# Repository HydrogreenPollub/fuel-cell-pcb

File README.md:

## Fuel cell control unit PCB

CADLAB preview: [link](https://cadlab.io/project/27518)

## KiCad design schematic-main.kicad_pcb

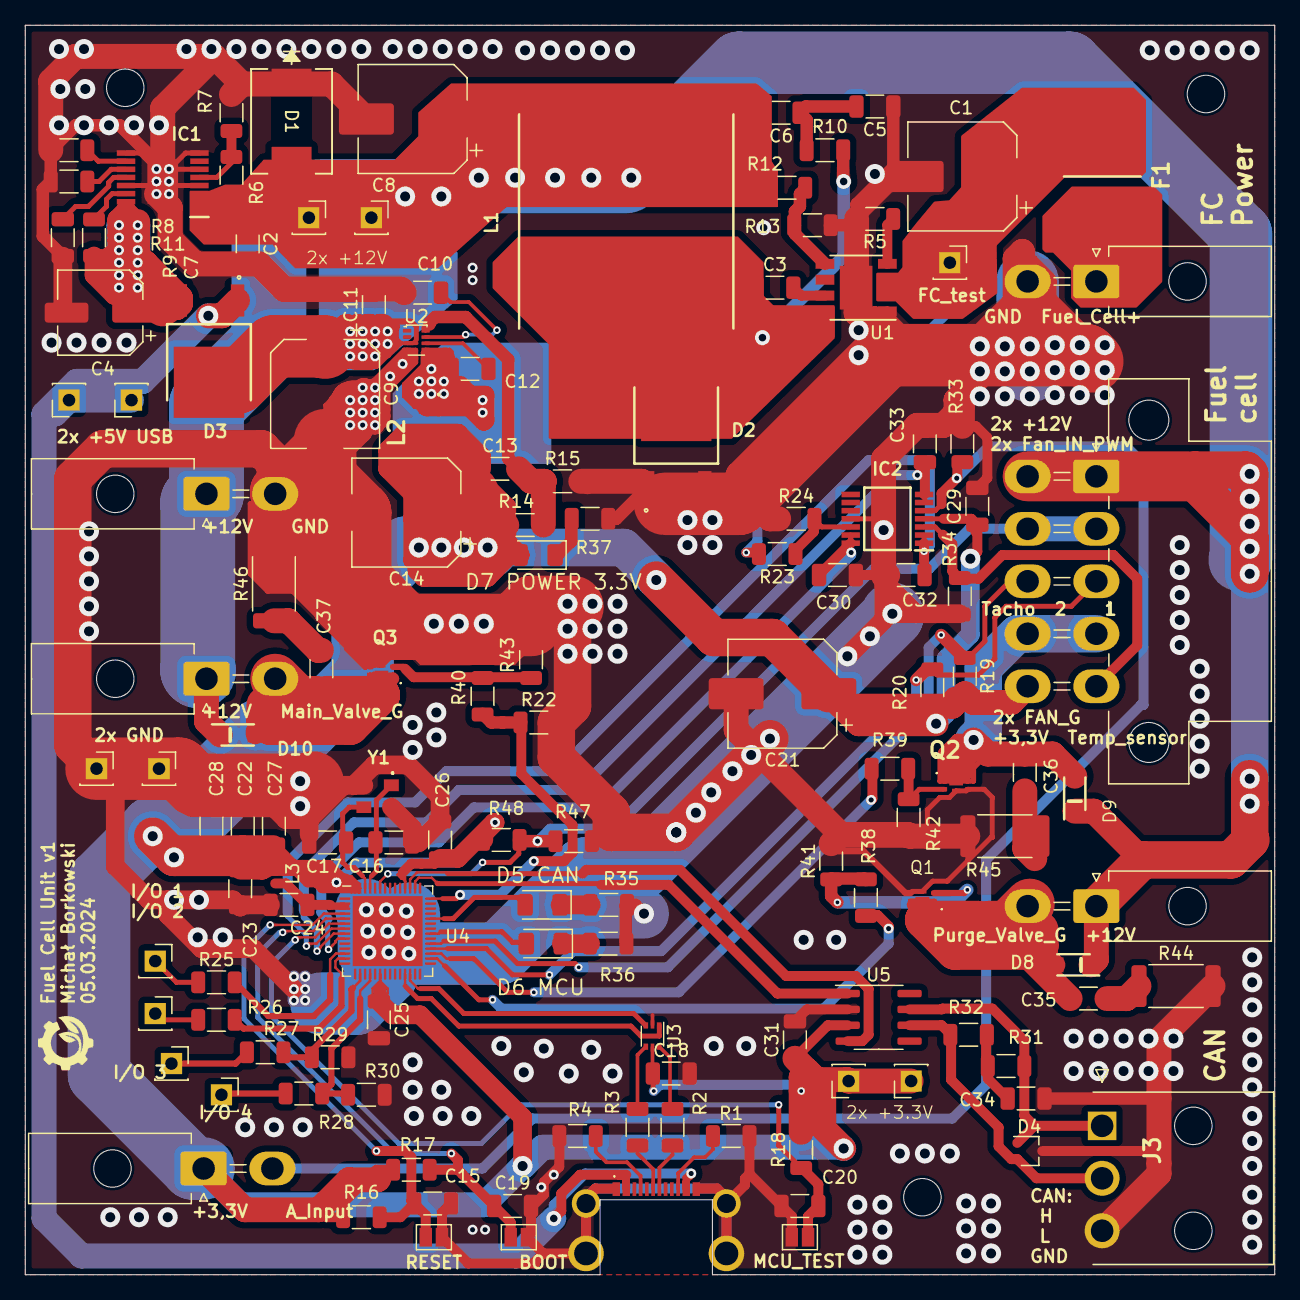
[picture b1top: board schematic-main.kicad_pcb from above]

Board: 2 copper layers, 100.0 x 100.0 mm, 133 parts (0 on the bottom side), 73 nets.

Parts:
C1, C9, C21: 10u; CP_Elec_8x10.5
C2, C15, C19, C20, C22, C27: 1u; C_1206_3216Metric
C3: 2n2; C_1206_3216Metric
C4: 47u; CP_Elec_6.3x7.7
C5, C13: 47p; C_1206_3216Metric
C6: 3n3; C_1206_3216Metric
C7: 2n7; C_1206_3216Metric
C8: 22u; CP_Elec_8x10.5
C10: 33n; C_1206_3216Metric
C11, C12, C18, C23, C24, C25, C26, C29, C31: 100n; C_1206_3216Metric
C14: 100u; CP_Elec_8x10.5
C16, C17: 12p; C_1206_3216Metric
C28: 10n; C_1206_3216Metric
C30, C32, C33, C34: 4n7; C_1206_3216Metric
C35, C36, C37: 20n; C_1206_3216Metric
D1: TPSMC30CA; TPSMCSeries_LTF
D2, D3: MBRD20100CT-13; TO252_(DPAK)_1
D4: SP0502BAJT; SOT-323_SC-70
D5 CAN, D6 MCU, D7 POWER 3.3V: LED; LED_1206_3216Metric
D8, D9, D10: PMEG10020; PMEG10020ELR
F1: 3A; FUSC8664X180N
IC1: LM76202QPWPRQ1; SOP65P640X120-17N
IC2: AD8544ARUZ-REEL; SOP65P640X120-14N
J1: Fell_Cell_IN; Molex_Mini-Fit_Jr_5569-02A2_2x01_P4.20mm_Horizontal
J2: Analog_In; Molex_Mini-Fit_Jr_5569-02A2_2x01_P4.20mm_Horizontal
J3: CAN; 39303035
J4: Axilary_Out; Molex_Mini-Fit_Jr_5569-02A2_2x01_P4.20mm_Horizontal
J5: P_Valve; Molex_Mini-Fit_Jr_5569-02A2_2x01_P4.20mm_Horizontal
J6: Valve; Molex_Mini-Fit_Jr_5569-02A2_2x01_P4.20mm_Horizontal
J7: FC Cooling; Molex_Mini-Fit_Jr_5569-10A1_2x05_P4.20mm_Horizontal
JP1, JP2, JP3: SolderJumper_2_Open; SolderJumper-2_P1.3mm_Open_Pad1.0x1.5mm
L1: IHLP6767DZER470M11
L2: 4u7; SRN3015TA4R7M
L3: 2n; L_0402_1005Metric
P1: USB_C_Plug_USB2.0; 2169900002
Q1, Q2, Q3: PMPB10XNX; PMPB15XPAX
R1, R4: 5k1; R_1206_3216Metric
R2, R3: 0; R_1206_3216Metric
R5, R8, R9: 100k; R_1206_3216Metric
R6: 180k; R_1206_3216Metric
R7: 12k; R_1206_3216Metric
R10: 143k; R_1206_3216Metric
R11: 56k; R_1206_3216Metric
R12: 453k; R_1206_3216Metric
R13: 49k9; R_1206_3216Metric
R14: 32k; R_1206_3216Metric
R15, R16, R17, R18, R19, R20, R22, R23, R29, R30, R33, R41, R42, R43, R47, R48: 10k; R_1206_3216Metric
R24: 150k; R_1206_3216Metric
R25, R26, R35, R36, R37: 1k; R_1206_3216Metric
R27, R28: 100R; R_1206_3216Metric
R31, R32: 60; R_1206_3216Metric
R34: 560k; R_1206_3216Metric
R38, R39, R40: 180R; R_1206_3216Metric
R44, R45, R46: 100R 0,5W; R_2512_6332Metric
TP1: I/O 1; PinSocket_1x01_P2.54mm_Vertical
TP1#2: FC test; PinSocket_1x01_P2.54mm_Vertical
TP2: I/O 2; PinSocket_1x01_P2.54mm_Vertical
TP2#2, TP3: GND; PinSocket_1x01_P2.54mm_Vertical
TP4, TP5: +12V; PinSocket_1x01_P2.54mm_Vertical
TP6, TP7: +5V; PinSocket_1x01_P2.54mm_Vertical
TP8, TP9: +3.3V; PinSocket_1x01_P2.54mm_Vertical
TP12: I/O 3; PinSocket_1x01_P2.54mm_Vertical
TP13: I/O 4; PinSocket_1x01_P2.54mm_Vertical
U1: LM5013DDAR; Diodes_SO-8EP
U2: TPS62933; SOT-583-8
U3: USBLC6-2P6; SOT-666
U4: ESP32-S3FN8; QFN-56-1EP_7x7mm_P0.4mm_EP5.6x5.6mm
U5: SN65HVD232; SOIC-8_3.9x4.9mm_P1.27mm
Y1: Crystal_GND24; KC3225K400000C1GE00

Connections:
+3.3V: C13.1, C14.1, C18.1, C21.1, C22.1, C23.1, C25.1, C26.1, C27.1, C28.1, C29.1, C31.1, D7 POWER 3.3V.2 (A), IC2.4 (V+), J2.1, J7.10, L2.2, L3.1, R14.1, R16.2, R17.2, R18.2, R19.2, R20.2, R48.2, TP8.1, TP9.1, U3.5 (VBUS), U4.20 (VDD3P3_RTC), U4.46 (VDD3P3_CPU), U4.55 (VDDA), U4.56 (VDDA), U5.3 (VCC)
+5V: D3.1, P1.A4 (VBUS), P1.A9 (VBUS), P1.B4 (VBUS), P1.B9 (VBUS), TP6.1, TP7.1
+12V: C2.1, C6.2, C8.1, D1.2 (A), D8.1 (K), D9.1 (K), D10.1 (K), IC1.1 (IN_1), IC1.2 (IN_2), IC1.3 (UVLO), J4.1, J5.1, J6.1, J7.1, J7.6, L1.2, R6.1, R12.2, TP4.1, TP5.1
/IO/A_Input: IC2.5 (+IN_B), J2.2, R33.1
/IO/Analog_MCU: C33.1, IC2.6 (-IN_B), IC2.7 (OUT_B), U4.8 (GPIO3/ADC1_CH2)
/IO/CANH: D4.1 (K), J3.1, R31.2, U5.7 (CANH)
/IO/CANL: D4.2 (K), J3.2, R32.2, U5.6 (CANL)
/IO/CAN_RX: U4.44 (MTCK/JTAG/GPIO39), U5.1 (D)
/IO/CAN_TX: U4.45 (MTDO/JTAG/GPIO40), U5.4 (R)
/IO/FAN_1_TACHO: J7.3, R20.1, U4.32 (SPICS0/GPIO29)
/IO/FAN_2_TACHO: J7.8, R19.1, U4.33 (SPICLK/GPIO30)
/IO/FAN_GND: C36.1, D9.2 (A), J7.4, J7.9, Q2.1 (D)
/IO/FAN_IN_PWM: J7.2, J7.7, R47.1, R48.1, U4.51 (GPIO45)
/IO/FAN_ON_MCU: R39.2, U4.31 (SPIWP/GPIO28)
/IO/FC_V: C1.1, F1.2, R23.2, TP1#2.1, U1.2 (VIN), U1.3 (EN_UVLO)
/IO/FC_Voltage_MCU: C30.2, IC2.13 (-IN_D), IC2.14 (OUT_D), U4.9 (GPIO4/ADC1_CH3)
/IO/I/O_1_MCU: R25.2, U4.12 (GPIO7/ADC1_CH6)
/IO/I/O_2_MCU: R26.2, U4.13 (GPIO8/ADC1_CH7)
/IO/I/O_3_MCU: R27.2, R29.1, U4.16 (GPIO11/ADC2_CH0)
/IO/I/O_4_MCU: R28.2, R30.1, U4.18 (GPIO13/ADC2_CH2)
/IO/LED_CAN_STATUS: D5 CAN.2 (A), U4.38 (GPIO33)
/IO/LED_MCU_STATUS: D6 MCU.2 (A), U4.35 (SPID/GPIO32)
/IO/Main_Valve: C37.1, D10.2 (A), J6.2, Q3.1 (D)
/IO/Main_Valve_MCU: R22.1, R40.2, U4.42 (GPIO37)
/IO/PURGE_VALVE: C35.1, D8.2 (A), J5.2, Q1.1 (D)
/IO/PURGE_VALVE_MCU: R38.2, U4.30 (SPIHD/GPIO27)
/IO/Temp_MCU: C32.2, IC2.1 (OUT_A), IC2.2 (-IN_A), U4.7 (GPIO2/ADC1_CH1)
/IO/Temp_sensor: IC2.3 (+IN_A), J7.5, R34.1
/MCU/BOOT: C19.1, JP2.1 (A), R17.1, U4.5 (GPIO0/BOOT)
/MCU/MCU_TEST: C20.1, JP3.1 (A), R18.1, U4.6 (GPIO1/ADC1_CH0)
/MCU/RESET: C15.1, JP1.1 (A), R16.1, U4.4 (CHIP_PU/RESET)
/MCU/USB_D+: R3.2, U3.3 (I/O2), U3.4 (I/O2), U4.26 (GPIO20/USB_D+/ADC2_CH9)
/MCU/USB_D-: R2.2, U3.1 (I/O1), U3.6 (I/O1), U4.25 (GPIO19/USB_D-/ADC2_CH8)
/MCU/XTAL_N: C16.1, U4.53 (XTAL_N), Y1.1
/MCU/XTAL_P: C17.1, U4.54 (XTAL_P), Y1.3
/Power /FB_12: R12.1, R13.2, U1.5 (FB)
/Power /Vin: F1.1, J1.1
/Power /Vreg: C4.1, D3.2, IC1.15 (OUT_1), IC1.16 (OUT_2), R9.1
GND: C1.2, C2.2, C4.2, C5.1, C7.2, C8.2, C9.2, C10.2, C11.2, C14.2, C15.2, C16.2, C17.2, C18.2, C19.2, C20.2, C21.2, C22.2, C23.2, C24.2, C25.2, C26.2, C27.2, C28.2, C29.2, C30.1, C31.2, C32.1, C33.2, C34.2, D1.1 (K), D2.1 (A_1), D2.2 (A_2), D4.3 (A), IC1.4 (NC_1), IC1.6 (MODE), IC1.8 (RTN), IC1.9 (GND), IC1.13 (NC_2), IC1.17 (EP), IC2.11 (GND), J1.2, J3.3, J4.2, JP1.2 (B), JP2.2 (B), JP3.2 (B), P1.A1 (GND), P1.A12 (GND), P1.B1 (GND), P1.B12 (GND), Q1.3 (S), Q2.3 (S), Q3.3 (S), R1.2, R4.2, R5.2, R7.2, R8.2, R11.2, R13.1, R15.2, R22.2, R24.1, R29.2, R30.2, R33.2, R34.2, R35.2, R36.2, R37.2, R41.2, R42.2, R43.2, R44.2, R45.2, R46.2, R47.2, TP2#2.1, TP3.1, U1.1 (GND), U1.9 (EP), U2.4 (GND), U3.2 (GND), U4.57 (GND), U5.2 (GND), Y1.2, Y1.4
unnamed: C5.2, C6.1, R10.2
unnamed: C34.1, R31.1, R32.1
unnamed: C35.2, R44.1
unnamed: C36.2, R45.1
unnamed: C37.2, R46.1
unnamed: C3.1, D2.3 (K), L1.1, R10.1, U1.8 (SW)
unnamed: D5 CAN.1 (K), R35.1
unnamed: D6 MCU.1 (K), R36.1
unnamed: D7 POWER 3.3V.1 (K), R37.1
unnamed: C7.1, IC1.12 (DVDT)
unnamed: IC1.11 (ILIM), R11.1
unnamed: IC1.10 (IMON), R8.1
unnamed: IC1.5 (OVP), R6.2, R7.1
unnamed: IC1.14 (~FLT), R9.2
unnamed: IC2.12 (+IN_D), R23.1, R24.2
unnamed: P1.A5 (CC), R4.1
unnamed: P1.A6 (D+), R3.1
unnamed: P1.A7 (D-), R2.1
unnamed: P1.B5 (VCONN), R1.1
unnamed: Q1.2 (G), R38.1, R41.1
unnamed: Q2.2 (G), R39.1, R42.1
unnamed: Q3.2 (G), R40.1, R43.1
unnamed: R25.1, TP1.1
unnamed: R26.1, TP2.1
unnamed: R27.1, TP12.1
unnamed: R28.1, TP13.1
unnamed: C3.2, U1.7 (BST)
unnamed: R5.1, U1.4 (RON)
unnamed: C12.1, U2.6 (BST)
unnamed: C13.2, R14.2, R15.1, U2.8 (FB)
unnamed: C10.1, U2.7 (SS)
unnamed: C12.2, L2.1, U2.5 (SW)
unnamed: C9.1, C11.1, D3.3, U2.3 (VIN)
VDD3P3: C24.1, L3.2, U4.2 (VDD3P3), U4.3 (VDD3P3)

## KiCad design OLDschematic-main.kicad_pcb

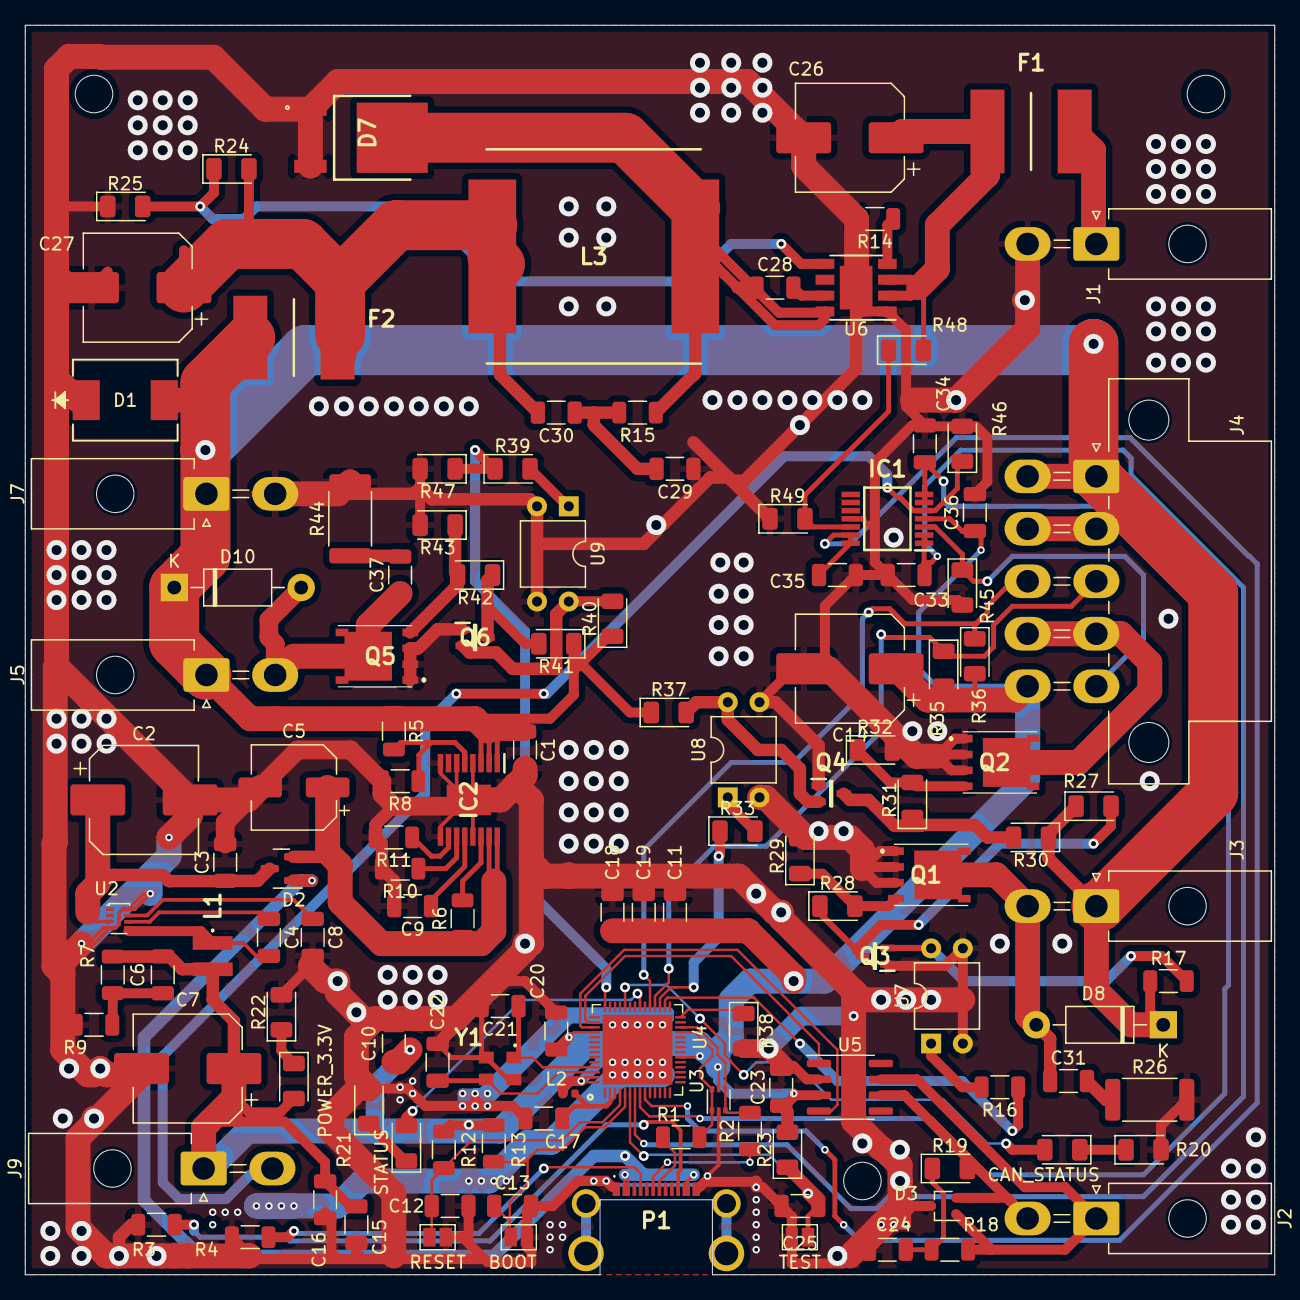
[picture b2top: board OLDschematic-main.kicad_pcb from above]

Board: 2 copper layers, 100.0 x 100.0 mm, 126 parts (0 on the bottom side), 75 nets.

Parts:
BOOT: SolderJumper_2_Open; SolderJumper-2_P1.3mm_Open_Pad1.0x1.5mm
C1, C12, C13, C15, C18, C25: 1u; C_1206_3216Metric
C2, C14, C26: 10u; CP_Elec_8x10.5
C3, C4, C10, C11, C16, C17, C20, C23, C36: 100n; C_1206_3216Metric
C5: 47u; CP_Elec_6.3x7.7
C6, C29: 47p; C_1206_3216Metric
C7: 100u; CP_Elec_8x10.5
C8: 33n; C_1206_3216Metric
C9: 2n7; C_1206_3216Metric
C19: 10n; C_1206_3216Metric
C21, C22: 12p; C_1206_3216Metric
C24, C33, C34, C35: 4n7; C_1206_3216Metric
C27: 22u; CP_Elec_8x10.5
C28: 2n2; C_1206_3216Metric
C30: 3n3; C_1206_3216Metric
C31, C37: 20n; C_1206_3216Metric
CAN_STATUS: LED; D_1206_3216Metric
D1: TPSMC30CA; TPSMCSeries_LTF
D2: BAS40-05; SOT-23
D3: SP0502BAJT; SOT-323_SC-70
D7: MBRD20100CT-13; TO252_(DPAK)_1
D8, D10: 1N5819; D_DO-41_SOD81_P10.16mm_Horizontal
F1, F2: 3A; FUSC8664X180N
IC1: AD8544ARUZ-REEL; SOP65P640X120-14N
IC2: LM76202QPWPRQ1; SOP65P640X120-17N
J1: Fell_Cell_IN; Molex_Mini-Fit_Jr_5569-02A2_2x01_P4.20mm_Horizontal
J2: CAN; Molex_Mini-Fit_Jr_5569-02A2_2x01_P4.20mm_Horizontal
J3: P_Valve; Molex_Mini-Fit_Jr_5569-02A2_2x01_P4.20mm_Horizontal
J4: FC Cooling; Molex_Mini-Fit_Jr_5569-10A1_2x05_P4.20mm_Horizontal
J5: Valve; Molex_Mini-Fit_Jr_5569-02A2_2x01_P4.20mm_Horizontal
J7: Axilary_Out; Molex_Mini-Fit_Jr_5569-02A2_2x01_P4.20mm_Horizontal
J9: Analog_In; Molex_Mini-Fit_Jr_5569-02A2_2x01_P4.20mm_Horizontal
L1: 4u7; SRN3015TA4R7M
L2: 2n; L_0402_1005Metric
L3: IHLP6767DZER470M11
P1: USB_C_Plug_USB2.0; 2169900002
POWER_3.3V: LED; D_1206_3216Metric
Q1, Q2, Q5: SIR186LDP-T1-RE3; SI7141DPT1GE3
Q3, Q4, Q6: 2N3904; SOT65P220X100-3N
R1, R2: 0; R_1206_3216Metric
R3, R4: 5k1; R_1206_3216Metric
R5: 180k; R_1206_3216Metric
R6, R11, R14: 100k; R_1206_3216Metric
R7: 32k; R_1206_3216Metric
R8: 12k; R_1206_3216Metric
R9, R12, R13: 10k; R_1206_3216Metric
R10: 56k; R_1206_3216Metric
R15: 143k; R_1206_3216Metric
R16: 100; R_1206_3216Metric
R17: 1k; R_1206_3216Metric
R18: 60; R_1206_3216Metric
R19: 60; LED_1206_3216Metric
R20, R21, R22, R27, R30, R37, R40, R41: 1k; LED_1206_3216Metric
R23, R29, R32, R35, R36, R38, R43, R46, R47, R48: 10k; LED_1206_3216Metric
R24: 453k; LED_1206_3216Metric
R25: 49k9; LED_1206_3216Metric
R26, R44: 100R 0,5W; R_2512_6332Metric
R28, R31, R33, R39, R42: 100; LED_1206_3216Metric
R45: 560k; LED_1206_3216Metric
R49: 150k; LED_1206_3216Metric
RESET: SolderJumper_2_Open; SolderJumper-2_P1.3mm_Open_Pad1.0x1.5mm
STATUS: LED; D_1206_3216Metric
TEST: SolderJumper_2_Open; SolderJumper-2_P1.3mm_Open_Pad1.0x1.5mm
U2: TPS62933; SOT-583-8
U3: USBLC6-2P6; SOT-666
U4: ESP32-S3FN8; QFN-56-1EP_7x7mm_P0.4mm_EP5.6x5.6mm
U5: SN65HVD232; SOIC-8_3.9x4.9mm_P1.27mm
U6: LM5013DDAR; Diodes_SO-8EP
U7, U8, U9: PC817; DIP-4_W7.62mm
Y1: Crystal_GND24; KC3225K400000C1GE00

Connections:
+3.3V: C6.1, C7.1, C10.1, C11.1, C14.1, C15.1, C16.1, C18.1, C19.1, C20.1, C23.1, C36.1, IC1.4 (V+), J4.10, J9.1, L1.2, L2.1, POWER_3.3V.2 (A), R7.1, R12.2, R13.2, R23.2, R35.2, R36.2, U3.5 (VBUS), U4.20 (VDD3P3_RTC), U4.46 (VDD3P3_CPU), U4.55 (VDDA), U4.56 (VDDA), U5.3 (VCC)
+12V: C1.1, D1.2 (A), D8.1 (K), D10.1 (K), F2.2, IC2.1 (IN_1), IC2.2 (IN_2), IC2.3 (UVLO), J3.1, J4.1, J4.6, J5.1, J7.1, R5.1, R17.1, R27.1, R30.1, R37.1, R40.1, R41.1
/FAN_PWM: J4.2, J4.7
/IO/A_Input: IC1.5 (+IN_B), J9.2, R46.1
/IO/Analog_MCU: C34.1, IC1.6 (-IN_B), IC1.7 (OUT_B), U4.8 (GPIO3/ADC1_CH2)
/IO/CANH: D3.1 (K), J2.1, R18.2, U5.7 (CANH)
/IO/CANL: D3.2 (K), J2.2, R19.2, U5.6 (CANL)
/IO/CAN_RX: U4.44 (MTCK/JTAG/GPIO39), U5.1 (D)
/IO/CAN_TX: U4.45 (MTDO/JTAG/GPIO40), U5.4 (R)
/IO/FAN_1_TACHO: J4.3, R35.1, U4.32 (SPICS0/GPIO29)
/IO/FAN_2_TACHO: J4.8, R36.1, U4.33 (SPICLK/GPIO30)
/IO/FAN_GND: J4.4, J4.9, Q2.5 (D_1), Q2.6 (D_2), Q2.7 (D_3), Q2.8 (D_4), Q2.9 (D_5), Q2.10 (D_6), Q2.11 (D_7)
/IO/FAN_ON_MCU: R33.1, U4.31 (SPIWP/GPIO28)
/IO/FC_Voltage_MCU: C35.2, IC1.13 (-IN_D), IC1.14 (OUT_D), U4.9 (GPIO4/ADC1_CH3)
/IO/LED_CAN_STATUS: CAN_STATUS.2 (A), U4.38 (GPIO33)
/IO/LED_MCU_STATUS: STATUS.2 (A), U4.35 (SPID/GPIO32)
/IO/Main_Valve: C37.1, D10.2 (A), J5.2, Q5.5 (D_1), Q5.6 (D_2), Q5.7 (D_3), Q5.8 (D_4), Q5.9 (D_5), Q5.10 (D_6), Q5.11 (D_7)
/IO/Main_Valve_MCU: R39.1, R47.1, U4.42 (GPIO37)
/IO/PURGE_VALVE: C31.1, D8.2 (A), J3.2, Q1.5 (D_1), Q1.6 (D_2), Q1.7 (D_3), Q1.8 (D_4), Q1.9 (D_5), Q1.10 (D_6), Q1.11 (D_7)
/IO/PURGE_VALVE_MCU: R16.1, U4.30 (SPIHD/GPIO27)
/IO/SC_V: C26.1, F1.2, R48.2, U6.2 (VIN), U6.3 (EN_UVLO)
/IO/Temp_MCU: C33.2, IC1.1 (OUT_A), IC1.2 (-IN_A), U4.7 (GPIO2/ADC1_CH1)
/IO/Temp_sensor: IC1.3 (+IN_A), J4.5, R45.1
/MCU/BOOT: BOOT.1 (A), C13.1, R13.1, U4.5 (GPIO0/BOOT)
/MCU/FAN_PWM_MCU: R38.1, U4.28 (SPI_CS1/GPIO26)
/MCU/MCU_TEST: C25.1, R23.1, TEST.1 (A), U4.6 (GPIO1/ADC1_CH0)
/MCU/RESET: C12.1, R12.1, RESET.1 (A), U4.4 (CHIP_PU/RESET)
/MCU/USB_D+: R2.2, U3.3 (I/O2), U3.4 (I/O2), U4.26 (GPIO20/USB_D+/ADC2_CH9)
/MCU/USB_D-: R1.2, U3.1 (I/O1), U3.6 (I/O1), U4.25 (GPIO19/USB_D-/ADC2_CH8)
/MCU/XTAL_N: C21.1, U4.53 (XTAL_N), Y1.1
/MCU/XTAL_P: C22.1, U4.54 (XTAL_P), Y1.3
/Power /FB_12: R24.1, R25.2, U6.5 (FB)
/Power /Vin: F1.1, J1.1
/Power /Vreg: C5.1, D2.2, IC2.15 (OUT_1), IC2.16 (OUT_2), R6.1
/VBUS: D2.1, P1.A4 (VBUS), P1.A9 (VBUS), P1.B4 (VBUS), P1.B9 (VBUS)
GND: BOOT.2 (B), C1.2, C2.2, C3.2, C5.2, C7.2, C8.2, C9.2, C10.2, C11.2, C12.2, C13.2, C14.2, C15.2, C16.2, C17.2, C18.2, C19.2, C20.2, C21.2, C22.2, C23.2, C24.2, C25.2, C26.2, C27.2, C29.1, C33.1, C34.2, C35.1, C36.2, D1.1 (K), D3.3 (A), D7.1 (A_1), D7.2 (A_2), IC1.11 (V-), IC2.4 (NC_1), IC2.6 (MODE), IC2.8 (RTN), IC2.9 (GND), IC2.13 (NC_2), IC2.17 (EP), J1.2, J7.2, P1.A1 (GND), P1.A12 (GND), P1.B1 (GND), P1.B12 (GND), Q1.1 (S_1), Q1.2 (S_2), Q1.3 (S_3), Q2.1 (S_1), Q2.2 (S_2), Q2.3 (S_3), Q3.1 (E), Q4.1 (E), Q5.1 (S_1), Q5.2 (S_2), Q5.3 (S_3), Q6.1 (E), R3.2, R4.2, R8.2, R9.2, R10.2, R11.2, R14.2, R20.2, R21.2, R22.2, R25.1, R26.2, R29.2, R32.2, R38.2, R43.2, R44.2, R45.2, R46.2, R47.2, R49.1, RESET.2 (B), TEST.2 (B), U2.4 (GND), U2.8 (FB), U3.2 (GND), U4.57 (GND), U5.2 (GND), U6.1 (GND), U6.9 (EP), U7.2, U7.3, U8.2, U8.3, U9.2, U9.3, Y1.2, Y1.4
unnamed: C24.1, R18.1, R19.1
unnamed: C27.1, C30.2, F2.1, L3.2, R24.2
unnamed: C29.2, C30.1, R15.2
unnamed: C31.2, R26.1
unnamed: C37.2, R44.1
unnamed: CAN_STATUS.1 (K), R20.1
unnamed: R21.1, STATUS.1 (K)
unnamed: POWER_3.3V.1 (K), R22.1
unnamed: C28.1, D7.3 (K), L3.1, R15.1, U6.8 (SW)
unnamed: IC1.12 (+IN_D), R48.1, R49.2
unnamed: C9.1, IC2.12 (DVDT)
unnamed: IC2.11 (ILIM), R10.1
unnamed: IC2.10 (IMON), R11.1
unnamed: IC2.5 (OVP), R5.2, R8.1
unnamed: IC2.14 (~FLT), R6.2
unnamed: P1.A5 (CC), R4.1
unnamed: P1.A6 (D+), R2.1
unnamed: P1.A7 (D-), R1.1
unnamed: P1.B5 (VCONN), R3.1
unnamed: Q1.4 (G), R28.2, R29.1
unnamed: Q2.4 (G), R31.2, R32.1
unnamed: Q3.2 (B), R17.2, U7.4
unnamed: Q3.3 (C), R27.2, R28.1
unnamed: Q4.2 (B), R37.2, U8.4
unnamed: Q4.3 (C), R30.2, R31.1
unnamed: Q5.4 (G), R42.2, R43.1
unnamed: Q6.2 (B), R40.2, U9.4
unnamed: Q6.3 (C), R41.2, R42.1
unnamed: R16.2, U7.1
unnamed: R33.2, U8.1
unnamed: R39.2, U9.1
unnamed: C4.1, U2.6 (BST)
unnamed: C6.2, R7.2, R9.1
unnamed: C8.1, U2.7 (SS)
unnamed: C4.2, L1.1, U2.5 (SW)
unnamed: C2.1, C3.1, D2.3, U2.3 (VIN)
unnamed: C28.2, U6.7 (BST)
unnamed: R14.1, U6.4 (RON)
VDD3P3: C17.1, L2.2, U4.2 (VDD3P3), U4.3 (VDD3P3)

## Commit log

2023-11-15 Update project structure to fit its name
2023-11-21 Add power stages
    Valve, power supplay, fan
2023-11-22 Add tags
    Edit main schema and sockets
2023-12-19 Add Schottky Diode for VBUS and Vreg
2024-01-24 Add FC voltage measure, axilary input and output
    Schematic complet?
2024-01-24 First pcb, change fan conector
2024-01-25 Change FC connector to 10pin & ideal diode sircuit
2024-01-26 Complate frist version
2024-01-30 porawa library
2024-02-07 Edit main
2024-02-10 Valve driver
2024-02-26 New pcb 1
2024-02-26 Power stage pcb complate
2024-03-02 New pcb 2
    Near complate
2024-03-05 New pcb 3
    Full connections and logotypes
2024-03-10 New pcb 4
2024-03-12 New pcb 5
2024-03-23 New pcb 6 end
2024-03-30 DRC tested
2024-03-30 Stencil 4x pcb
2024-04-05 Rename and send to production
